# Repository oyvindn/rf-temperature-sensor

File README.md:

# Battery driven wireless temperature sensor

Arduino based battery driven wireless temperature sensor.

## Introduction

## ATmega328 on a breadboard

In order to save battery the ATmega328P is set to use its internal 8 MHz RC oscillator as a clock. This way we can set up a minimal circuit, eliminating the need for extra components like the the 16 MHz crystal. See the [From Arduino to a Microcontroller on a Breadboard](https://docs.arduino.cc/built-in-examples/arduino-isp/ArduinoToBreadboard) tutorial for instructions on how to burn a bootloader and setting up the minimal ATmega328 circuit on a breadboard.

## Hardware

* ATmega328P
* HopeRF RFM69CW 13DBM 868Mhz RF Transceiver Module
* DS18B20 Digital temperature sensor

## Arduino sketch dependencies

* [Arduino AVR Boards](https://github.com/arduino/ArduinoCore-avr)
* [RadioHead Packet Radio library for embedded microprocessors](http://www.airspayce.com/mikem/arduino/RadioHead/)
* [One Wire](https://github.com/PaulStoffregen/OneWire)
* [Arduino Library for Maxim Temperature Integrated Circuits](https://github.com/milesburton/Arduino-Temperature-Control-Library)
* [Low-Power](https://github.com/rocketscream/Low-Power)

## Compile, upload and monitor ATmega328p using the Arduino CLI

### Add secrets
Copy `arduino_secrets.h.example` to `arduino_secrets.h` and change the example secret values.

### Download and install Arduino IDE and/or CLI
[Arduino CLI](https://arduino.github.io/arduino-cli/) is an all-in-one solution that provides Boards/Library Managers, sketch builder, board detection, uploader, and many other tools needed to use any Arduino compatible board and platform from command line or machine interfaces.

## Download and burn bootloader
Download the [ATmega328 on a breadboard bootloader](https://www.arduino.cc/en/uploads/Tutorial/breadboard-1-6-x.zip) and follow the instructions in the [From Arduino to a Microcontroller on a Breadboard](https://docs.arduino.cc/built-in-examples/arduino-isp/ArduinoToBreadboard) tutorial.

### Install library dependecies
Install the library dependencies listet above.

### Compile sketch
`arduino-cli compile -b breadboard:avr:atmega328bb`

### Upload sketch to ATmega328P using e.g. a FTD-232R-3V3 USB to TTL Serial Cable:
`arduino-cli upload -p /dev/cu.usbserial-FTC0DLEV -b breadboard:avr:atmega328bb -v`

### Open the serial monitor
`arduino-cli monitor -p /dev/cu.usbserial-FTC0DLEV -c baudrate=115200`

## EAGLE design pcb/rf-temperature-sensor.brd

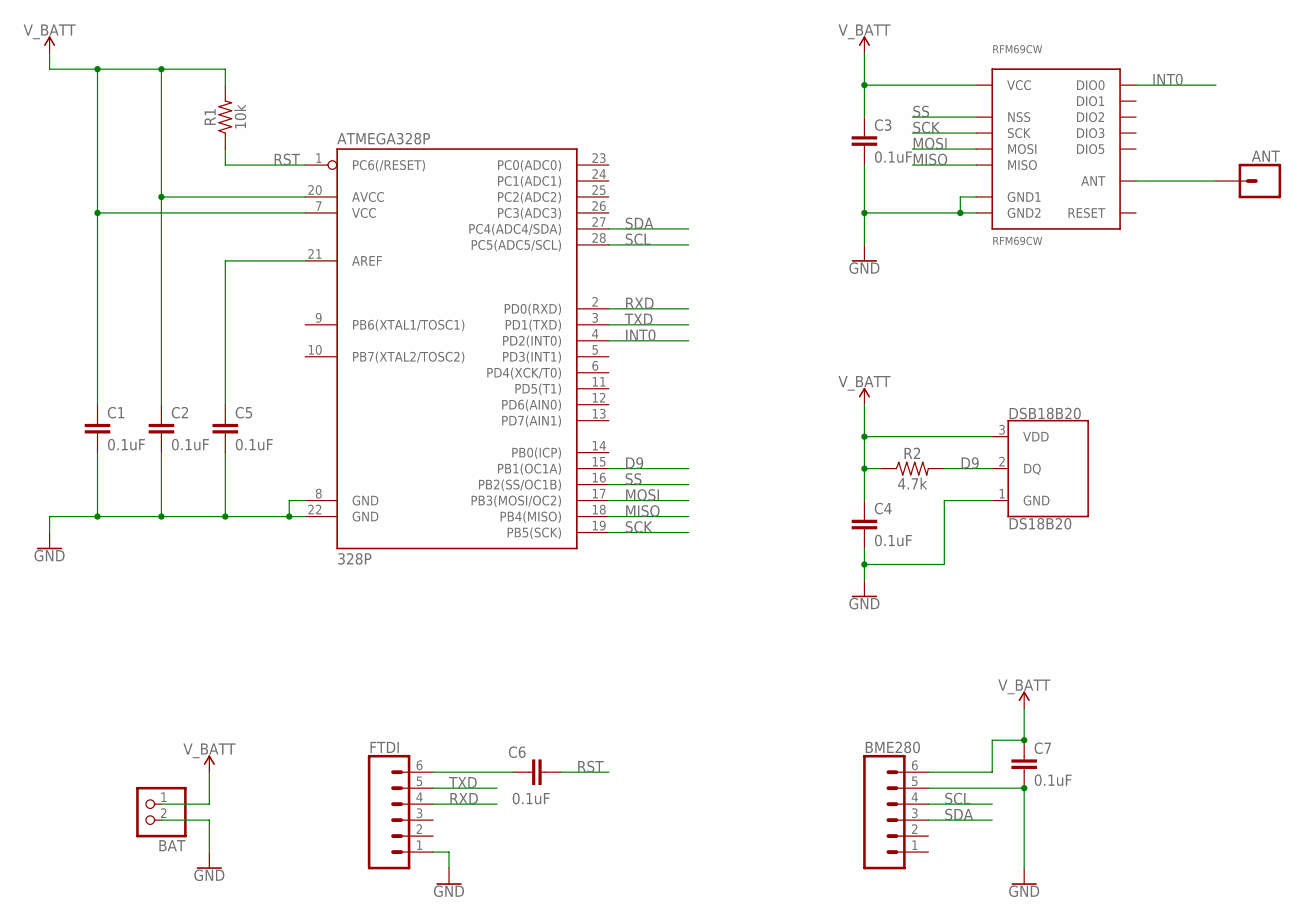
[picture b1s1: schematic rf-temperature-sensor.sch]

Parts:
ANT: CONN_01; 1X01
ATMEGA328P: 328P; DIP28
BAT: JST_2PIN-THM-RA; JST-PH-2-THM-RA
BME280: CONN_06SILK_FEMALE_PTH; 1X06
C1, C2, C3, C4, C5, C6, C7: 0.1uF; 0603
DSB18B20: DS18B20; TO-92-AMMO
FTDI: CONN_06SILK_FEMALE_PTH; 1X06
R1: 10k; 0603
R2: 4.7k; 0603
RFM69CW: RFM69CW

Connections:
D9: ATMEGA328P.15 (PB1(OC1A)), DSB18B20.2 (DQ), R2.2
GND: ATMEGA328P.8 (GND), ATMEGA328P.22 (GND), BAT.2 (1), BME280.5, C1.2, C2.2, C3.2, C4.2, C5.2, C7.2, DSB18B20.1 (GND), FTDI.1, RFM69CW.GND@1 (GND1), RFM69CW.GND@2 (GND2)
INT0: ATMEGA328P.4 (PD2(INT0)), RFM69CW.DIO0
MISO: ATMEGA328P.18 (PB4(MISO)), RFM69CW.MISO
MOSI: ATMEGA328P.17 (PB3(MOSI/OC2)), RFM69CW.MOSI
unnamed: ATMEGA328P.21 (AREF), C5.1
unnamed: ANT.1, RFM69CW.ANT
unnamed: C6.1, FTDI.6
RST: ATMEGA328P.1 (PC6(/RESET)), C6.2, R1.1
RXD: ATMEGA328P.2 (PD0(RXD)), FTDI.4
SCK: ATMEGA328P.19 (PB5(SCK)), RFM69CW.SCK
SCL: ATMEGA328P.28 (PC5(ADC5/SCL)), BME280.4
SDA: ATMEGA328P.27 (PC4(ADC4/SDA)), BME280.3
SS: ATMEGA328P.16 (PB2(SS/OC1B)), RFM69CW.NSS
TXD: ATMEGA328P.3 (PD1(TXD)), FTDI.5
V_BATT: ATMEGA328P.7 (VCC), ATMEGA328P.20 (AVCC), BAT.1 (2), BME280.6, C1.1, C2.1, C3.1, C4.1, C7.1, DSB18B20.3 (VDD), R1.2, R2.1, RFM69CW.VDD (VCC)

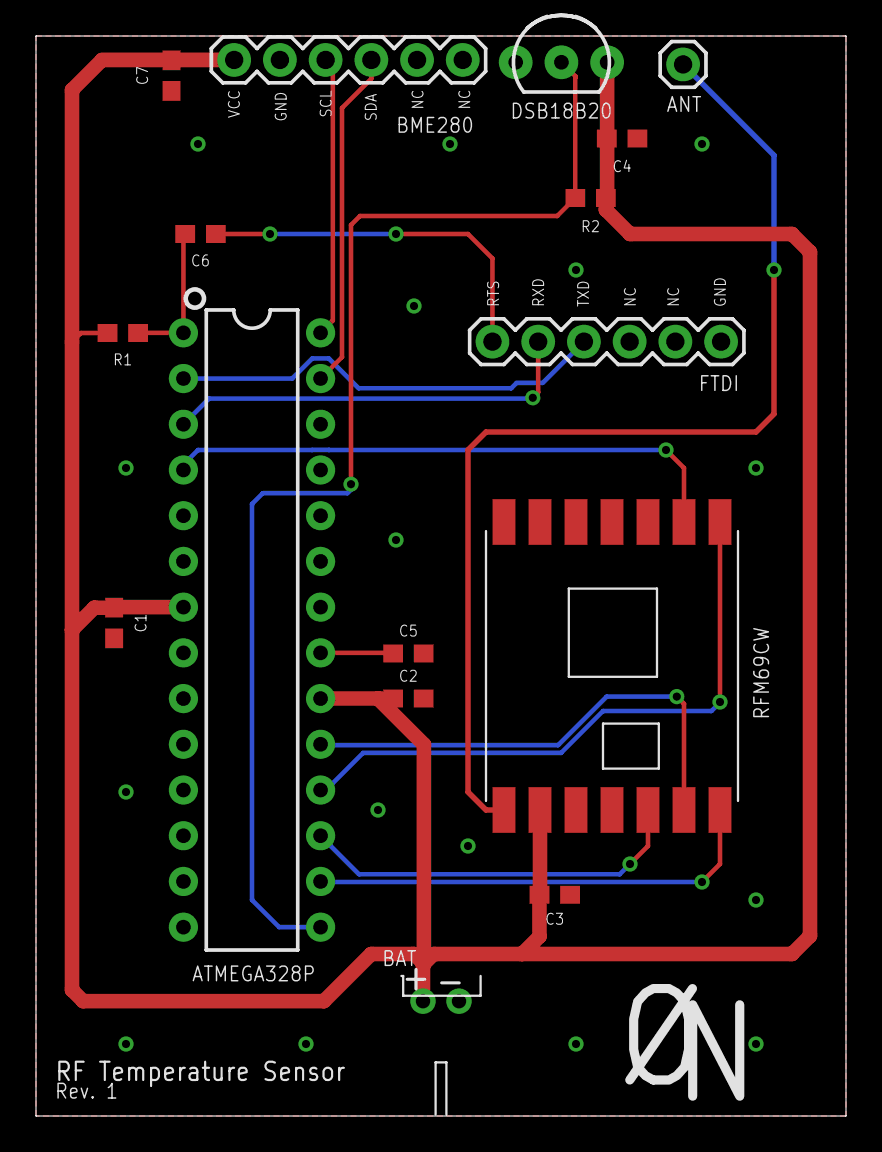
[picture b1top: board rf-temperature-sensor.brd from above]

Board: 2 copper layers, 45.0 x 60.0 mm, 16 parts (0 on the bottom side), 16 nets.

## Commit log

2022-03-04 Inital sketch code
2022-03-15 Change server/client naming
2022-03-15 Rename ino file
2022-03-16 Flush serial before powering down
2022-03-16 Fix constant name
2022-03-17 Power down for 5 minutes (38 times 8 seconds)
2022-03-18 Remove serial print in main loop to save battery
2022-04-04 Add support for BME280 Humidity, Barometric Pressure and Temperature sensor
2022-04-08 Add message type and send all sensor data
2022-05-28 add pcb design
2022-06-28 Use the 868 MHz ISM band
2022-06-28 Add MHz on print output

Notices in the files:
parts and their libraries:
SparkFun-Connectors: Licensing: Creative Commons ShareAlike 4.0 International - https://creativecommons.org/licenses/by-sa/4.0
